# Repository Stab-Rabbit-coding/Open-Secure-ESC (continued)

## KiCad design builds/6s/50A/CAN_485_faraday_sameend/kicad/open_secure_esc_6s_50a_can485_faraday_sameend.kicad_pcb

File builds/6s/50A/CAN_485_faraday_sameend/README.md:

# Build: 6S / 50A / CAN-FD + RS-485 / Faraday / Same-end egress

Governed by [`AGENTS.md`](../../../../AGENTS.md). Per-build instantiation of
the axis options in the repo-root [`README.md`](../../../../README.md),
walked from [`docs/decision-matrix.xlsx`](../../../../docs/decision-matrix.xlsx).

**Parent build:** [`../CAN_485_faraday/`](../CAN_485_faraday/). This variant
differs on exactly one axis — **Wire Egress** — and inherits that build's
entire BOM, schematic and verification state. The BOM is deliberately **not**
duplicated here; it would drift. Read the parent's `README.md` for every part
and its citation, and treat this document as the delta only.

**Status: NOT READY FOR FABRICATION.** Geometry is applied and DRC-clean of
errors; two nets at the new terminal end are still unconnected by design (§4),
and the board has no stackup (§5). AI-generated by **Claude Opus 5**
(Anthropic), 2026-08-31. Not human-reviewed.

## Requested build parameters

| Axis | Selection | Same as parent? |
| --- | --- | --- |
| Voltage | 6S | yes |
| Amperage | 50A | yes |
| Protocol | CAN-FD **and** RS-485 | yes |
| Control | *not specified* | yes |
| EMI Hardening | Faraday | yes |
| **Wire Egress** | **Same-end, opposite faces** | **NO — this variant** |

## 1. What "same-end, opposite faces" means here

All five 50 A conductors leave the same board end, for a pocket (blind-cavity)
installation with no access to the far end. The two groups are separated by
putting them on **opposite faces** with the board's two inner GND planes
between them:

| Conductor | Net | Face | Position |
| --- | --- | --- | --- |
| `PH_A` | phase A | F.Cu | (25.45, 90.50) mm |
| `PH_B` | phase B | F.Cu | (35.95, 90.50) mm |
| `PH_C` | phase C | F.Cu | (46.45, 90.50) mm |
| `VM` (VBATT+) | pack + | **B.Cu** | (30.95, 90.50) mm |
| `GND` (VBATT−) | pack − | **B.Cu** | (40.95, 90.50) mm |

Rationale, coupling arithmetic, and the rejected alternatives are in
[`docs/design-single-end-wire-egress-variant.md`](../../../../docs/design-single-end-wire-egress-variant.md).

## 2. The board is longer, not re-partitioned

The design document's original plan moved `U1`/`U2`/`J1` to the logic end to
free the terminal end. **That plan is dead.** `U1`'s courtyard measures
13.45 mm, not the 12.90 mm the envelope calculation assumed, so with `U1` at
the logic end `docs/tools/isolation_envelope.py` returns:

```text
13.45 + 2 x (7.5 + 1.43) + 2 x 0.55 = 32.41 mm minimum board width
```

against an actual 32.00 mm — a **0.41 mm failure**. The 7.5 mm creepage
underneath it is REFERENCES.md [9] Table 6, a verified primary-source value,
so the board width cannot absorb it. The design document's own instruction for
this case is explicit: *"this variant needs a different partition, not a wider
board."*

The different partition is to leave the logic cluster where it is and buy
**length** at the terminal end. `isolation_envelope.py` prices width against
length at 2.7× on this geometry, so length is the cheap dimension.

| | Parent | This variant |
| --- | --- | --- |
| Board outline | 1.260 × 2.602 in (32.00 × 66.10 mm) | 1.260 × 2.996 in (32.00 × 76.10 mm) |
| Board area | 3.28 in² (2115 mm²) | 3.77 in² (2435 mm²), **+15.1 %** |
| `U1` / `U2` / `J1` | B.Cu, y ≈ 76–86 mm | **unchanged** |
| MCU → gate-driver run | ≈18.5 mm | **unchanged** |
| Current-sense returns | — | **unchanged** |

Leaving the logic cluster alone also drops both regressions the original
partition carried.

Applied by [`kicad/tools/make_same_end_egress.py`](kicad/tools/make_same_end_egress.py).

## 3. Inner planes are the interface shield

At the terminal end `In1.Cu` and `In2.Cu` are both solid GND, so two grounded
planes lie between the phase pads on F.Cu and the pack pads on B.Cu. A
grounded plane does not attenuate the field between two conductors — it
terminates it.

This only works because the inner-layer copper-pour keepout was removed from
the parent build first (commit `4baa178`,
[`../CAN_485_faraday/kicad/tools/restore_inner_planes.py`](../CAN_485_faraday/kicad/tools/restore_inner_planes.py)).
Before that, the rule area forbade pour on **all four** copper layers across
the terminal window, so the shield had a hole in it exactly where this variant
needs it. Probe points inside the window went 0/6 → 6/6 in copper on both
inner planes.

## 4. Open: VM distribution to the relocated pack pad

**Two nets at the new terminal end are unconnected, both known and neither
bridged by guesswork.**

| Net | Pad | Why |
| --- | --- | --- |
| `VM` | `J5A` pin 1 | The VM pour stops at y 60.3 mm (F.Cu) and y 60.5 mm (In2.Cu); B.Cu from y 60.5 mm to the board end is GND. Carrying VM to a B.Cu pad in the new terminal band re-partitions a plane, which depends on a stackup this board does not have (§5). |
| `GND` | `J5B` pin 1 | The outer-layer rule area moved with the terminal band and now blocks the B.Cu GND pour from reaching the pad — the same defect `TODO.md` 12.5.an measures on the parent, where pour meets a J4 pad over 1.00 mm of a 10 mm pad. |

Neither was closed with a track. `docs/tools/conductor_sizing.py` shows a
0.118 in (3.0 mm) track across that span costs 11.36 W across three phases —
more than all six TPHR8504PL FETs' 10.5 W conduction loss combined. That
copper must be pour, or the terminal must sit on the pour's layer.

Both point at the same unresolved decision: `TODO.md` 12.5.ae, whether the
outer-layer (F.Cu/B.Cu) extent of the rule area should be deleted or shrunk.
That moves 50 A current paths and is reserved for sign-off. **This build
inherits that open decision from its parent.**

## 5. Open: the board has no stackup

The `.kicad_pcb` declares four copper layers and carries `(thickness 1.6)` in
its `general` block, which is KiCad's default rather than a design decision.
No dielectric height, copper weight, laminate permittivity or surface finish
is specified anywhere in this repository. Tracked as `TODO.md` 15.2; it gates
the copper-weight and fabrication decisions.

## 6. Verification state

Toolchain pinned to **KiCad 9.0.2** throughout (`/usr/bin/kicad-cli`,
`pcbnew 9.0.2+dfsg-1`). The board file remains `version 20241229` /
`generator_version "9.0"` and has **not** been advanced to KiCad 10.

| Check | Parent | This variant |
| --- | --- | --- |
| DRC violations | 20 | **20** |
| DRC errors | 0 | **0** |
| DRC warnings | 20 (11 silk_over_copper, 7 silk_overlap, 2 isolated_copper) | identical |
| Unconnected items | 151 | **150** |

The two `solder_mask_bridge` errors introduced by the first geometry pass were
traced to fiducials `FID3`/`FID6`, which sat inside the old rule-area band and
were engulfed once that band flooded with copper. They move with the band;
step 6 of the tool does this and the errors are gone.

**Routing is not complete on either build** — 150 unconnected items is
inherited, not caused by this variant. This build is not a routed board and
must not be read as one.

## 7. Not done

- Routing and re-pour after route (parent is also unrouted).
- Gerber generation — `gerbers/` is a placeholder.
- Connector selection: `J4`/`J5` are still bare solder-wire pads
  (`TODO.md` 12.4.l), and single-end egress tightens the constraint.
- Common-mode choke on the pack input, mandatory for this variant
  (`TODO.md` 15.7).
- Conducted-emissions pre-compliance; the parent's result does not transfer.

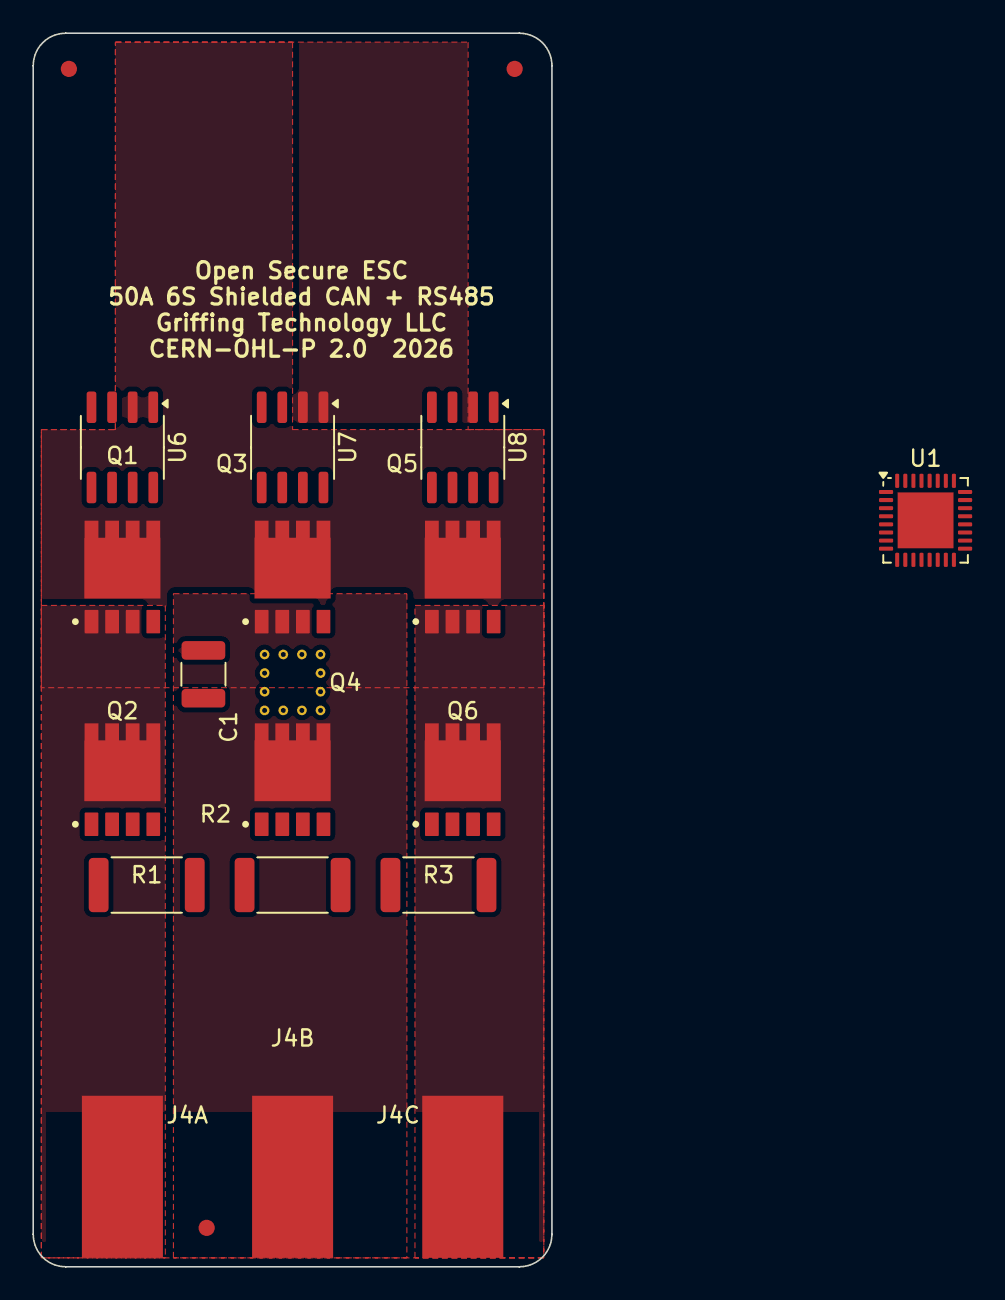
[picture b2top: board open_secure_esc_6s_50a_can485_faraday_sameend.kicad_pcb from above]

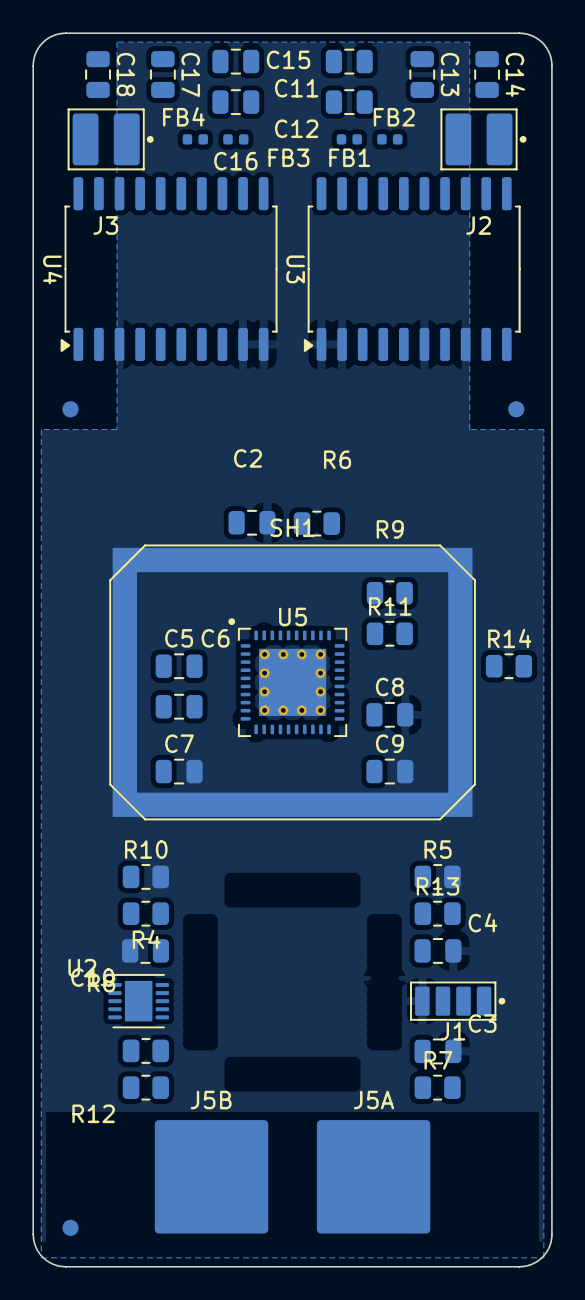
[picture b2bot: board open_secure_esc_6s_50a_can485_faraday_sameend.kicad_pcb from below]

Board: 4 copper layers, 32.0 x 76.1 mm, 65 parts (45 on the bottom side), 62 nets, no tracks yet.

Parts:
C1: C_1210_3225Metric
C2, C3, C4, C5, C6, C7, C8, C9, C10: C_0805_2012Metric
C11, C15: 10uF; C_0805_2012Metric
C12: 220nF; C_0805_2012Metric
C13, C16, C17: 100nF; C_0805_2012Metric
C14, C18: 10nF; C_0805_2012Metric
FB1, FB2, FB3, FB4: BLM15HD182SN1D; L_0402_1005Metric
FID1, FID2, FID3, FID4, FID5, FID6: Fiducial_1mm_Mask2mm
J1: SolderPad_1x04_SMD_P1.27mm_Probe
J2, J3: SolderPad_1x02_SMD_P2.54mm
J4A, J4B, J4C: SolderWirePad_1x01_SMD_5x10mm
J5A, J5B: SolderWire-6sqmm_1x01_D3.5mm_OD7mm
Q1, Q2, Q3, Q4, Q5, Q6: Toshiba_2-5W1A_SOP-Advance-N_5.15x6.1mm_P1.27mm
R1, R2, R3: R_2512_6332Metric
R4, R5, R6, R7, R8, R9, R10, R11, R12, R13, R14: R_0805_2012Metric
SH1: Wurth_WE-SHC_3670209_Frame_15.3x20.9mm
U1: MSPM0G3518_Q1_RHB; Texas_RHB0032E_VQFN-32-1EP_5x5mm_P0.5mm_EP3.45x3.45mm
U2: Infineon_PG-USON-10-2-4_3x3mm_P0.5mm_EP1.7x2.5mm
U3, U4: SOIC-20W_7.5x12.8mm_P1.27mm
U5: TI_RTA0040B_WQFN-40_6x6mm_P0.5mm_EP4.15x4.15mm
U6, U7, U8: SOIC-8_3.9x4.9mm_P1.27mm

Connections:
3V3: C2.1, C4.1, C10.1, J1.3, R4.1, R6.1, R7.1, R9.1, R11.1, R12.1, R13.1, R14.1, U1.4, U2.10, U3.3, U3.4, U4.2, U4.8, U6.6, U7.6, U8.6
ADC_IU: U1.28, U6.5
ADC_IV: U1.27, U7.5
ADC_IW: U1.29, U8.5
CAN_GNDISO: C11.2, C12.2, FB2.1, U3.18, U3.20
CAN_ISO_GND: C13.2, C14.2, FB2.2, U3.11, U3.12, U3.15
CAN_VISOIN: C13.1, C14.1, FB1.2, U3.16
CAN_VISOOUT: C11.1, C12.1, FB1.1, U3.19
GD_SPI_MISO: R14.2, U1.20, U5.27
GND: C1.2, C2.2, C3.2, C4.2, C7.2, C8.2, C9.2, C10.2, J1.4, J5B.1, R1.2, R2.2, R3.2, R5.2, R10.2, SH1.1, U1.5, U2.1, U3.1, U3.2, U3.6, U3.8, U3.10, U4.1, U4.3, U4.9, U4.10, U5.10, U5.11, U5.20, U5.25, U5.39, U5.41, U6.1, U6.2, U7.1, U7.2, U8.1, U8.2
ISENSE_A_HI: Q2.1, Q2.2, Q2.3, R1.1, U5.9, U6.8
ISENSE_B_HI: Q4.1, Q4.2, Q4.3, R2.1, U5.12, U7.8
ISENSE_C_HI: Q6.1, Q6.2, Q6.3, R3.1, U5.19, U8.8
NRST: R6.2, R7.2, U1.3
unnamed: J1.1, U1.23
unnamed: J1.2, U1.24
unnamed: J2.1, U3.14
unnamed: J2.2, U3.13
unnamed: Q1.4, U5.6
unnamed: Q2.4, U5.8
unnamed: Q3.4, U5.15
unnamed: Q4.4, U5.13
unnamed: Q5.4, U5.16
unnamed: Q6.4, U5.18
unnamed: U1.17, U3.5
unnamed: U1.16, U3.7
unnamed: U1.6, U5.30
unnamed: U1.22, U5.28
unnamed: U1.21, U5.29
unnamed: U1.12, U5.32
unnamed: U1.13, U5.33
unnamed: U1.7, U5.34
unnamed: U1.8, U5.35
unnamed: U1.14, U5.36
unnamed: U1.15, U5.37
unnamed: U1.2, U4.4
unnamed: U1.1, U4.7
unnamed: C5.1, U5.2
unnamed: C5.2, U5.1
unnamed: C8.1, U5.38
unnamed: R9.2, U5.31
unnamed: C6.1, U5.5
unnamed: C9.1, U5.40
unnamed: C7.1, U5.24
unnamed: R11.2, U5.26
PH_A: J4A.1, Q1.1, Q1.2, Q1.3, Q2.5, Q2.6, Q2.7, Q2.8, U5.7
PH_B: J4B.1, Q3.1, Q3.2, Q3.3, Q4.5, Q4.6, Q4.7, Q4.8, U5.14
PH_C: J4C.1, Q5.1, Q5.2, Q5.3, Q6.5, Q6.6, Q6.7, Q6.8, U5.17
RS485_A: J3.1, U4.13, U4.18
RS485_B: J3.2, U4.15, U4.17
RS485_DE_RE: U1.10, U4.5, U4.6
RS485_GNDISO: C15.2, C16.2, FB4.1, U4.11, U4.14
RS485_ISO_GND: C17.2, C18.2, FB4.2, U4.16, U4.20
RS485_VISOIN: C17.1, C18.1, FB3.2, U4.19
RS485_VISOOUT: C15.1, C16.1, FB3.1, U4.12
SE_I2C_SCL: R13.2, U1.19, U2.8
SE_I2C_SDA: R12.2, U1.9, U2.3
SE_RST: U1.18, U2.9
VBUS_SENSE: R8.2, R10.1, U1.25
VCORE: C3.1, U1.32
VM: C1.1, C6.2, J5A.1, Q1.5, Q1.6, Q1.7, Q1.8, Q3.5, Q3.6, Q3.7, Q3.8, Q5.5, Q5.6, Q5.7, Q5.8, R8.1, U5.3, U5.4
VREF_MID: R4.2, R5.1, U6.3, U6.7, U7.3, U7.7, U8.3, U8.7

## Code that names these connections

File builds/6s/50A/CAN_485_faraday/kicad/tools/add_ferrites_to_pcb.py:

#!/usr/bin/env python3
"""Push the isolated-supply ferrite change from the schematic into the PCB.

Governed by AGENTS.md. Companion to tools/add_isolated_supply_ferrites.py,
which made the same change on the sheet. Run that one first.

WHAT CHANGES
------------
Four BLM15HD182SN1D beads [53] are added, and the two isolated grounds are
split from one net into two, as [9] and [10] require:

    FB1  CAN_VISOOUT   -> CAN_VISOIN      U3 pin 19 -> pin 16
    FB2  CAN_GNDISO    -> CAN_ISO_GND     U3 pins 18,20 -> pins 11,15
    FB3  RS485_VISOOUT -> RS485_VISOIN    U4 pin 12 -> pin 19
    FB4  RS485_GNDISO  -> RS485_ISO_GND   U4 pins 11,14 -> pins 16,20

Pad-level net reassignment is done explicitly rather than by re-importing a
netlist, because a full netlist import would also rebuild footprint positions
and discard the repo owner's hand placement.

PLACEMENT IS PARKED, NOT SOLVED -- READ THIS
---------------------------------------------
[10] p.15 says of VISOOUT: "Connect this pin through a ferrite bead and short
the PCB trace to VISOIN for operation." There is nowhere short to put them.

Measured on this board: U3's isolated pin row sits at x = 11.28 and U4's at
x = 14.45, facing each other across 3.17 mm, with the two package courtyards
(U3 to x 12.59, U4 from x 13.14) leaving a 0.55 mm channel between them. No
0402 fits there, let alone four of them plus the eight capacitors [9] and [10]
also require. The nearest genuinely free back-side copper is a single
pocket at x 19.4..24.9, y 24.5..28.6 -- right of U2, above J1.

An earlier version of this script parked them at y 2.6/6.6 on the strength of
a free-space scan that only counted BACK-side footprints. That was wrong:
J5A and J5B are FRONT-side through-hole parts whose 7 x 7 mm pads and 4.4 mm
barrels block both sides, and the beads landed straight on top of them -- 8
shorting_items. The repo already documents this trap in
symbols/tools/gen_smd_solder_pad_footprints.py ("a through-hole part costs its
area TWICE"). Any occupancy scan on this board must include through-hole
footprints regardless of which side they are mounted on.

So this script parks the beads in that free space with correct nets, which
makes the design electrically complete and lets ERC/DRC and the router see
them. It does NOT satisfy the datasheets' trace-length guidance. Opening a
channel along the two isolated pin rows is a PLACEMENT change and belongs to
the repo owner -- TODO.md 12.5.af.

Usage:
    python3 tools/add_ferrites_to_pcb.py [--dry-run]
"""
# Authored by Claude Opus 5 (Anthropic) 2026-08-17, TODO.md 12.5.ad.
# AI-generated. Pin functions quoted are from the local copies of [9]/[10];
# all coordinates are measured off the board. Not human-authored.

import argparse
import math
import shutil
from pathlib import Path

import pcbnew

HERE = Path(__file__).resolve().parent
PCB = HERE.parent / "open_secure_esc_6s_50a_can485_faraday.kicad_pcb"
BACKUP = PCB.with_suffix(".kicad_pcb.pre-ferrite.bak")
FPLIB = "/usr/share/kicad/footprints/Inductor_SMD.pretty"
FPNAME = "L_0402_1005Metric"

# (ref, net on pad 1, net on pad 2, park x, park y, rotation)
FERRITES = [
    ("FB1", "CAN_VISOOUT", "CAN_VISOIN", 20.80, 25.30, 0),
    ("FB2", "CAN_GNDISO", "CAN_ISO_GND", 23.30, 25.30, 0),
    ("FB3", "RS485_VISOOUT", "RS485_VISOIN", 20.80, 27.30, 0),
    ("FB4", "RS485_GNDISO", "RS485_ISO_GND", 23.30, 27.30, 0),
]
# Pads whose net membership changes, per the datasheet pin tables.
RENET = {
    ("U3", "16"): "CAN_VISOIN",  # [10] VISOIN, fed from VISOOUT via FB1
    ("U3", "18"): "CAN_GNDISO",  # [10] GNDISO, dc-dc converter ground
    ("U3", "20"): "CAN_GNDISO",
    ("U4", "11"): "RS485_GNDISO",  # [9] GND2 converter side
    ("U4", "14"): "RS485_GNDISO",
    ("U4", "19"): "RS485_VISOIN",  # [9] VISOIN, fed from VISOOUT via FB3
}


def origin(board):
    """Top-left of the board outline."""
    box = board.GetBoardEdgesBoundingBox()
    return box.GetLeft(), box.GetTop()


def net(board, name):
    """Existing net by name, or a freshly created one."""
    info = board.GetNetInfo().GetNetItem(name)
    if info is not None:
        return info
    info = pcbnew.NETINFO_ITEM(board, name)
    board.Add(info)
    print(f"     created net {name}")
    return info


def main() -> int:
    """Add the beads, split the isolated grounds, report trace distances."""
    ap = argparse.ArgumentParser(description=__doc__)
    ap.add_argument("--dry-run", action="store_true")
    args = ap.parse_args()

    board = pcbnew.LoadBoard(str(PCB))
    ox, oy = origin(board)

    if any(f.GetReference().startswith("FB") for f in board.Footprints()):
        print("ferrites already present -- nothing to do")
        return 0

    print("1. re-netting U3/U4 pads to split the isolated grounds")
    done = 0
    for f in board.Footprints():
        ref = f.GetReference()
        for p in f.Pads():
            key = (ref, p.GetNumber())
            if key in RENET:
                old = p.GetNetname()
                p.SetNet(net(board, RENET[key]))
                print(f"     {ref}.{p.GetNumber()}: {old} -> {RENET[key]}")
                done += 1
    if done != len(RENET):
        raise SystemExit(f"expected {len(RENET)} pad re-nets, did {done}")

    print("\n2. adding the beads")
    for ref, n1, n2, x, y, rot in FERRITES:
        fp = pcbnew.FootprintLoad(FPLIB, FPNAME)
        if fp is None:
            raise SystemExit(f"could not load {FPLIB}/{FPNAME}")
        fp.SetReference(ref)
        fp.SetValue("BLM15HD182SN1D")
        board.Add(fp)
        fp.SetPosition(pcbnew.VECTOR2I(ox + pcbnew.FromMM(x), oy + pcbnew.FromMM(y)))
        fp.Flip(fp.GetPosition(), False)  # isolated section is on B.Cu
        if rot:
            fp.SetOrientationDegrees(rot)
        for p in fp.Pads():
            p.SetNet(net(board, n1 if p.GetNumber() == "1" else n2))
        print(f"     {ref} [{n1} | {n2}] parked at ({x}, {y}) on B.Cu")

    pcbnew.ZONE_FILLER(board).Fill(board.Zones())
    board.BuildConnectivity()

    print("\n3. distance from each bead to the pins it must sit near")
    pads = {}
    for f in board.Footprints():
        for p in f.Pads():
            pads.setdefault(p.GetNetname(), []).append(
                (f.GetReference(), p.GetNumber(), p.GetPosition())
            )
    for ref, n1, n2, x, y, _ in FERRITES:
        here = pcbnew.VECTOR2I(ox + pcbnew.FromMM(x), oy + pcbnew.FromMM(y))
        for n in (n1, n2):
            far = [
                (
                    math.hypot(pcbnew.ToMM(p.x - here.x), pcbnew.ToMM(p.y - here.y)),
                    r,
                    pn,
                )
                for r, pn, p in pads.get(n, [])
                if not r.startswith("FB")
            ]
            if far:
                d, r, pn = min(far)
                print(f"     {ref} -> {r}.{pn} ({n}): {d:5.1f} mm")
    print("\n   These are PARKED positions. [10] p.15 asks for a short trace")
    print("   to VISOIN; see this script's docstring and TODO.md 12.5.af.")

    if args.dry_run:
        print("\n--dry-run: nothing written")
        return 0
    shutil.copy2(PCB, BACKUP)
    board.Save(str(PCB))
    print(f"\nsaved {PCB.name} (backup: {BACKUP.name})")
    return 0


if __name__ == "__main__":
    raise SystemExit(main())

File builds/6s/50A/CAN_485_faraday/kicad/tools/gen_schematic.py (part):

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        b.wire((out_x, pb[1]), pb)
    rail(b, u4, "A", "right", "RS485_A")
    rail(b, u4, "B", "right", "RS485_B")
    rail(b, r["j_rs485"], "Pin_1", "left", "RS485_A")
    rail(b, r["j_rs485"], "Pin_2", "left", "RS485_B")
    rail_all(b, u4, "GND1", "left", "GND")
    rail_all(b, u4, "VCC", "left", "3V3")
    connect(b, u1, "RS485_TXD", u4, "TxD")
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    connect(b, u1, "PWM_CL", u5, "INLC")

    # ---- Phase legs (A/B/C): FETs, shunt, current sense -------------------------
    adc_pin = {"A": "ADC_IU", "B": "ADC_IV", "C": "ADC_IW"}
    drv_gh = {"A": "GHA", "B": "GHB", "C": "GHC"}
    drv_gl = {"A": "GLA", "B": "GLB", "C": "GLC"}
    drv_sh = {"A": "SHA", "B": "SHB", "C": "SHC"}
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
